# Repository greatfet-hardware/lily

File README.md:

# Lily
an RF power detecting GreatFET neighbor

Required KiCad dependency:

https://github.com/greatscottgadgets/gsg-kicad-lib

If you are using git, the preferred way to install gsg-kicad-lib is to use the
submodule:

```
git submodule init && git submodule update
```

## potential ICs
* LTC5507 100 kHz - 1 GHz
* HMC1120LP4E DC - 3.9 GHz
* MAX2016 LF - 2.5 GHz dual channel
* ADL5904 DC - 6 GHz
* AD8363 DC - 6 GHz
* HMC909LP4E DC - 5.8 GHz

## Pin usage

signal  | pin     | alt1  | alt2
--------|---------|-------|-----
VOUT    | J2.05   | J2.09 | J2.16
ENBL    | J1.03   | J1.04 | J1.05
RST     | GND     | J1.20 | J1.22
Q       |         | J2.17 | J2.18
Q bar   |         | J2.30 | J2.31

## Initial calibration data
Calibration data was taken by driving the RF input of Lily with a function generator creating a 10MHz sine wave at various amplitudes (VPP). The analog voltage output (VRMS) was measured with an oscilloscope and the ADC was used to convert VRMS into a digital measurement. Driving Lily with an input of VPP = 4V resulted in Lily drawing 4mA of supply current. The input should not exceed VPP = 5.62V in order to avoid damaging the board.

VPP     | VRMS    | ADC
--------|---------|-------
10mV    | 25mV    | 7
50mV    | 0.258V  | 84
0.1V    | 0.478V  | 155
0.2V    | 0.697V  | 227
0.3V    | 0.830V  | 267
0.5V    | 0.988V  | 317
1V      | 1.2V    | 386
2V      | 1.4V    | 454
3V      | 1.57V   | 494
4V      | 1.66V   | 524

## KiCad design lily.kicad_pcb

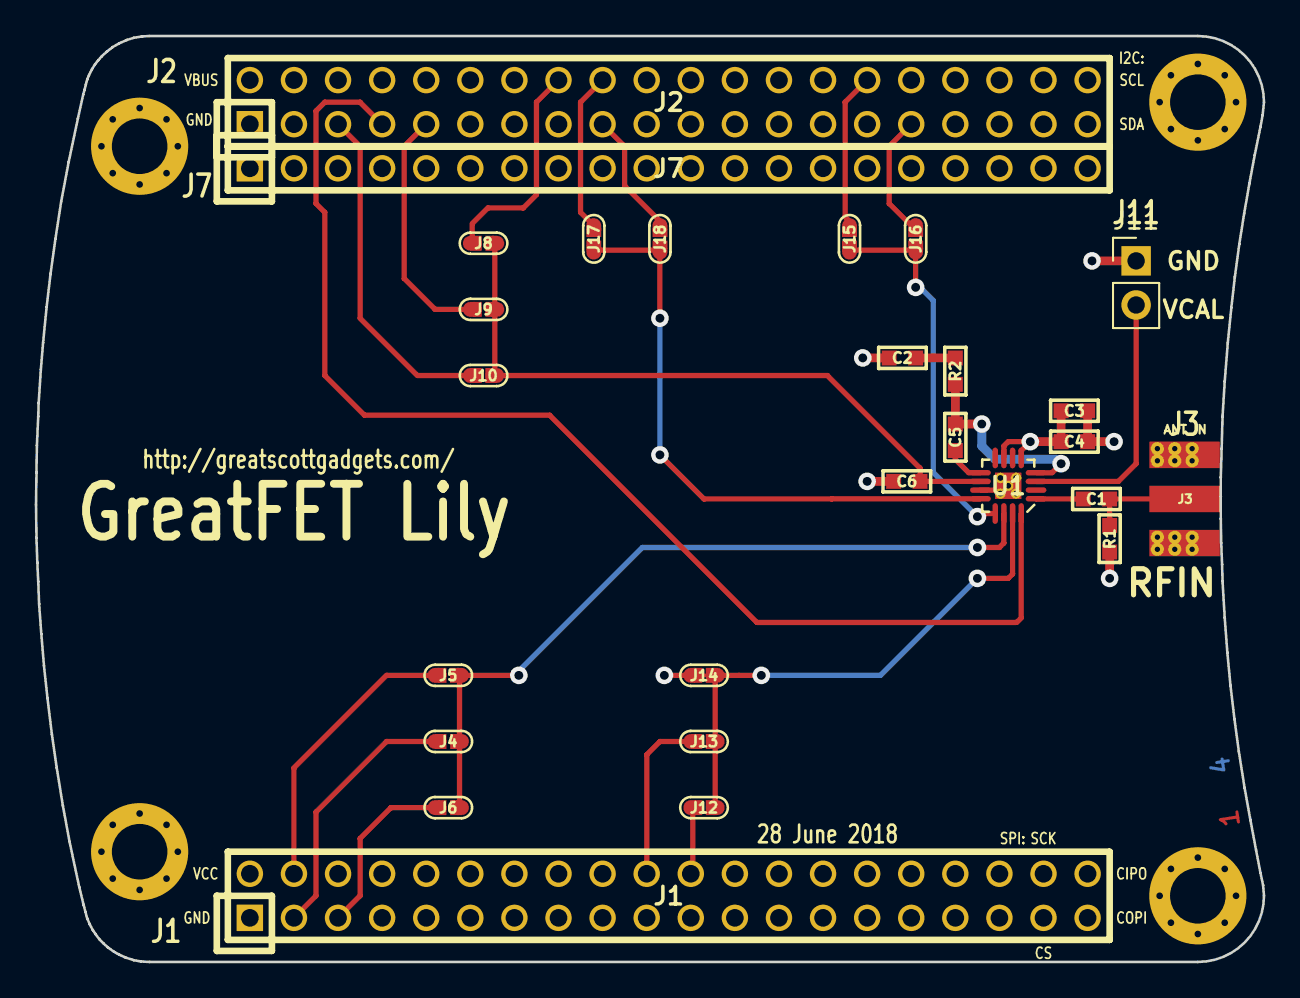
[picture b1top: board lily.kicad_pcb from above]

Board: 4 copper layers, 70.7 x 53.3 mm, 31 parts (0 on the bottom side), 26 nets.

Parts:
C1: 470nF; 0603
C2, C3, C5: 100nF; 0603
C4: 100pF; 0603
C6: 10nF; 0603
J1: NEIGHBOR1; HEADER-2x20
J2: NEIGHBOR2; HEADER-2x20
J3: ANT_IN; SMA-EDGE
J4, J5, J6, J8, J9, J10, J12, J13, J14, J15, J16, J17, J18: TEST_2P; 0603-JUMPER
J7: BONUS_ROW; HEADER-1x20
J11: Conn_01x02; Pin_Header_Straight_1x02_Pitch2.54mm
MH1, MH2, MH3, MH4: MOUNTING_HOLE; HOLE126MIL-COPPER
R1: 82.5; 0603
R2: 4.02; 0603
U1: ADL5904; QFN16-3

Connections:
/ADC0_0: J2.5, J10.2
/ENBL: J4.1, J5.1, J6.1, U1.14
/P0_0: J1.4, J5.2
/P1_10: J1.20, J13.1
/P1_11: J1.22, J12.1
/P2_5: J2.18, J17.2
/P3_7: J2.30, J15.2
/P4_3: J2.9, J9.2
/P4_4: J2.7, U1.16
/P4_9: J1.3, J4.2
/P4_10: J1.5, J6.2
/P6_7: J2.31, J16.2
/P7_7: J2.16, J8.2
/RF_IN: C1.1, U1.1
/VOUT: C6.1, J8.1, J9.1, J10.1, U1.10
/WAKEUP0: J2.17, J18.2
/rms_avg: C5.2, R2.1, U1.4
GND: C2.2, C3.2, C4.2, C6.2, J1.1, J2.1, J3.2, J7.1, J7.10, J7.19, J11.1, J14.1, MH1.1, MH2.1, MH3.1, MH4.1, R1.2, U1.0, U1.11
unnamed: C1.2, J3.1, R1.1
unnamed: C2.1, R2.2
unnamed: C5.1, U1.9
unnamed: J11.2, U1.3
unnamed: J12.2, J13.2, J14.2, U1.15
unnamed: J15.1, J16.1, U1.13
unnamed: J17.1, J18.1, U1.12
VCC: C3.1, C4.1, J1.2, J7.20, U1.5, U1.7

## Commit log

2019-05-27 split lily into separate repository
2019-05-27 updated README.md to be lily-specific
2019-09-06 move information from greatfet wiki to README
2020-07-03 adopt OSHWA convention for SPI signal names https://www.oshwa.org/a-resolution-to-redefine-spi-signal-names
